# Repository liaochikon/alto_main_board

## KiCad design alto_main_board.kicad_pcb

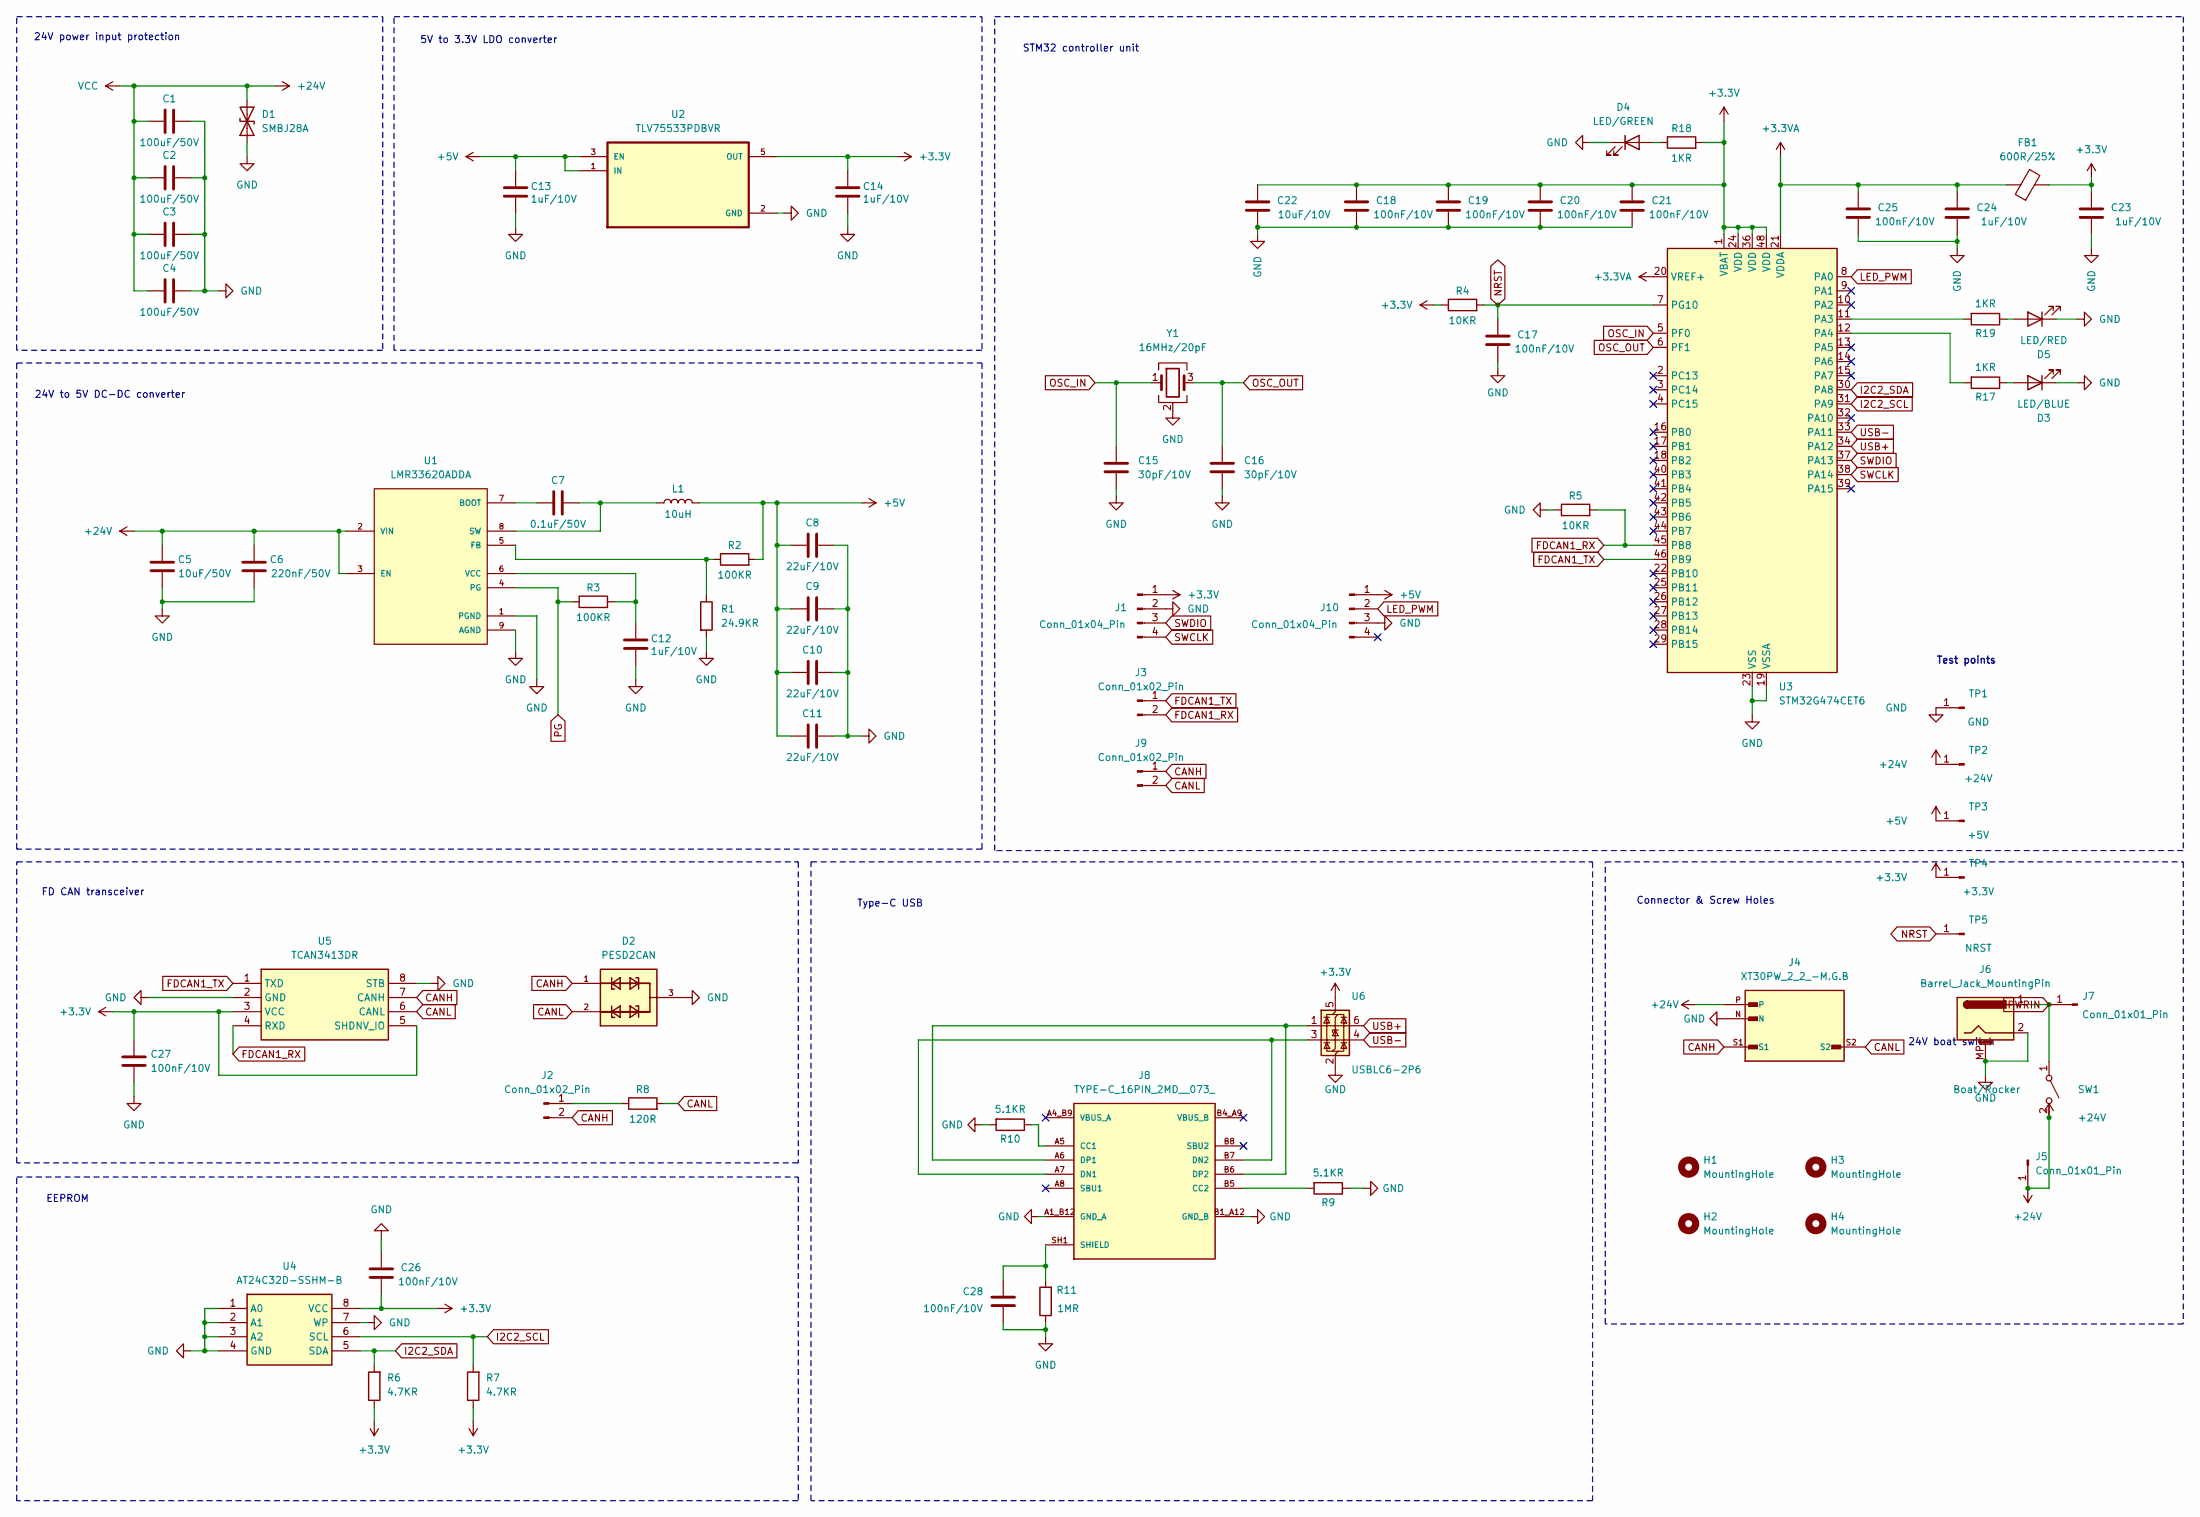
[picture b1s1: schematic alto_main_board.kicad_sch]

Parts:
C1, C2, C3, C4: 100uF/50V; C_1210_3225Metric
C5: 10uF/50V; C_0603_1608Metric
C6: 220nF/50V; C_0603_1608Metric
C7: 0.1uF/50V; C_0603_1608Metric
C8, C9, C10, C11: 22uF/10V; C_0603_1608Metric
C12, C13, C14, C23, C24: 1uF/10V; C_0603_1608Metric
C15, C16: 30pF/10V; C_0603_1608Metric
C17, C18, C19, C20, C21, C25, C26, C27, C28: 100nF/10V; C_0603_1608Metric
C22: 10uF/10V; C_0603_1608Metric
D1: SMBJ28A; D_SMB
D2: PESD2CAN; SOT95P230X110-3N
D3: LED/BLUE; LED_0603_1608Metric
D4: LED/GREEN; LED_0603_1608Metric
D5: LED/RED; LED_0603_1608Metric
FB1: 600R/25%; L_0603_1608Metric
H1, H2, H3, H4: MountingHole; MountingHole_3.2mm_M3
J1: Conn_01x04_Pin; PinHeader_1x04_P2.54mm_Vertical
J2, J3, J9: Conn_01x02_Pin; PinHeader_1x02_P2.54mm_Vertical
J4: XT30PW_2_2_-M.G.B; AMASS_XT30PW_2_2_-M.G.B; PARTREV NA
J5, J7: Conn_01x01_Pin; PinHeader_1x01_P2.54mm_Vertical
J6: Barrel_Jack_MountingPin; BarrelJack_Wuerth_694108106102_2.5x5.5mm
J8: TYPE-C_16PIN_2MD__073_; SHOUHAN_TYPE-C_16PIN_2MD__073_; PARTREV A
J10: Conn_01x04_Pin; JST_XH_B4B-XH-A_1x04_P2.50mm_Vertical
L1: 10uH; L_Chilisin_BWVS00505030
R1: 24.9KR; R_0603_1608Metric
R2, R3: 100KR; R_0603_1608Metric
R4, R5: 10KR; R_0603_1608Metric
R6, R7: 4.7KR; R_0603_1608Metric
R8: 120R; R_0603_1608Metric
R9, R10: 5.1KR; R_0603_1608Metric
R11: 1MR; R_0603_1608Metric
R17, R18, R19: 1KR; R_0603_1608Metric
SW1: Boat/Rocker
TP1: GND; PinHeader_1x01_P2.54mm_Vertical
TP2: +24V; PinHeader_1x01_P2.54mm_Vertical
TP3: +5V; PinHeader_1x01_P2.54mm_Vertical
TP4: +3.3V; PinHeader_1x01_P2.54mm_Vertical
TP5: NRST; PinHeader_1x01_P2.54mm_Vertical
U1: LMR33620ADDA; CONV_LMR33620ADDA; PARTREV C
U2: TLV75533PDBVR; SOT95P280X145-5N
U3: STM32G474CET6; LQFP-48_7x7mm_P0.5mm
U4: AT24C32D-SSHM-B; SOIC127P600X175-8N; Manufacturer_Part_Number AT24C32D-SSHM-B; Mouser Part Number 556-AT24C32D-SSHM-B
U5: TCAN3413DR; SOIC127P600X175-8N; Manufacturer_Part_Number TCAN3413DR; Mouser Part Number 595-TCAN3413DR
U6: USBLC6-2P6; SOT-23-6
Y1: 16MHz/20pF; Crystal_SMD_3225-4Pin_3.2x2.5mm

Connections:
+3.3V: C14.2, C18.1, C19.1, C20.1, C21.1, C22.1, C23.1, C26.2, C27.2, FB1.2, J1.1, R4.1, R6.1, R7.1, R18.2, TP4.1, U2.5 (OUT), U3.1 (VBAT), U3.24 (VDD), U3.36 (VDD), U3.48 (VDD), U4.8 (VCC), U5.3 (VCC), U5.5 (SHDNV_IO), U6.5 (VBUS)
+3.3VA: C24.1, C25.1, FB1.1, U3.20 (VREF+), U3.21 (VDDA)
+5V: C8.1, C9.1, C10.1, C11.1, C13.2, J10.1, L1.2, R2.2, TP3.1, U2.1 (IN), U2.3 (EN)
+24V: C1.1, C2.1, C3.1, C4.1, C5.1, C6.1, D1.2 (A2), J4.P, J5.1, SW1.2 (B), TP2.1, U1.2 (VIN), U1.3 (EN)
CANH: D2.1, J2.2, J4.S1, J9.1, U5.7 (CANH)
CANL: D2.2, J4.S2, J9.2, R8.2, U5.6 (CANL)
FDCAN1_RX: J3.2, R5.2, U3.45 (PB8), U5.4 (RXD)
FDCAN1_TX: J3.1, U3.46 (PB9), U5.1 (TXD)
GND: C1.2, C2.2, C3.2, C4.2, C5.2, C6.2, C8.2, C9.2, C10.2, C11.2, C12.1, C13.1, C14.1, C15.2, C16.2, C17.2, C18.2, C19.2, C20.2, C21.2, C22.2, C23.2, C24.2, C25.2, C26.1, C27.1, C28.2, D1.1 (A1), D2.3, D3.1 (K), D4.1 (K), D5.1 (K), J1.2, J4.N, J6.2, J6.MP (MountPin), J8.A1_B12 (GND_A), J8.B1_A12 (GND_B), J10.3, R1.2, R5.1, R9.1, R10.2, R11.1, TP1.1, U1.1 (PGND), U1.9 (AGND), U1.9_1 (AGND), U1.9_2 (AGND), U1.9_3 (AGND), U1.9_4 (AGND), U1.9_5 (AGND), U1.9_6 (AGND), U1.9_7 (AGND), U1.9_8 (AGND), U2.2 (GND), U3.19 (VSSA), U3.23 (VSS), U3.35 (VSS), U3.47 (VSS), U4.1 (A0), U4.2 (A1), U4.3 (A2), U4.4 (GND), U4.7 (WP), U5.2 (GND), U5.8 (STB), U6.2 (GND), Y1.2 (G), Y1.4 (G)
I2C2_SCL: R7.2, U3.31 (PA9), U4.6 (SCL)
I2C2_SDA: R6.2, U3.30 (PA8), U4.5 (SDA)
LED_PWM: J10.2, U3.8 (PA0)
unnamed: C28.1, J8.SH1 (SHIELD), J8.SH2 (SHIELD), J8.SH3 (SHIELD), J8.SH4 (SHIELD), R11.2
unnamed: D3.2 (A), R17.1
unnamed: D4.2 (A), R18.1
unnamed: D5.2 (A), R19.1
unnamed: J2.1, R8.1
unnamed: J6.1, J7.1, SW1.1 (A)
unnamed: J8.A5 (CC1), R10.1
unnamed: J8.B5 (CC2), R9.2
unnamed: J8.A7 (DN1), J8.B7 (DN2), U6.3 (I/O2)
unnamed: J8.A6 (DP1), J8.B6 (DP2), U6.1 (I/O1)
unnamed: C7.1, U1.7 (BOOT)
unnamed: R1.1, R2.1, U1.5 (FB)
unnamed: C7.2, L1.1, U1.8 (SW)
unnamed: C12.2, R3.2, U1.6 (VCC)
unnamed: R19.2, U3.11 (PA3)
unnamed: R17.2, U3.12 (PA4)
unnamed: C17.1, R4.2, TP5.1, U3.7 (PG10)
OSC_IN: C15.1, U3.5 (PF0), Y1.1
OSC_OUT: C16.1, U3.6 (PF1), Y1.3
PG: R3.1, U1.4 (PG)
SWCLK: J1.4, U3.38 (PA14)
SWDIO: J1.3, U3.37 (PA13)
USB+: U3.34 (PA12), U6.6 (I/O1)
USB-: U3.33 (PA11), U6.4 (I/O2)

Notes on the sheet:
Type-C USB
Connector & Screw Holes
24V to 5V DC-DC converter
5V to 3.3V LDO converter
EEPROM
24V power input protection
FD CAN transceiver
STM32 controller unit
24V boat switch
Test points

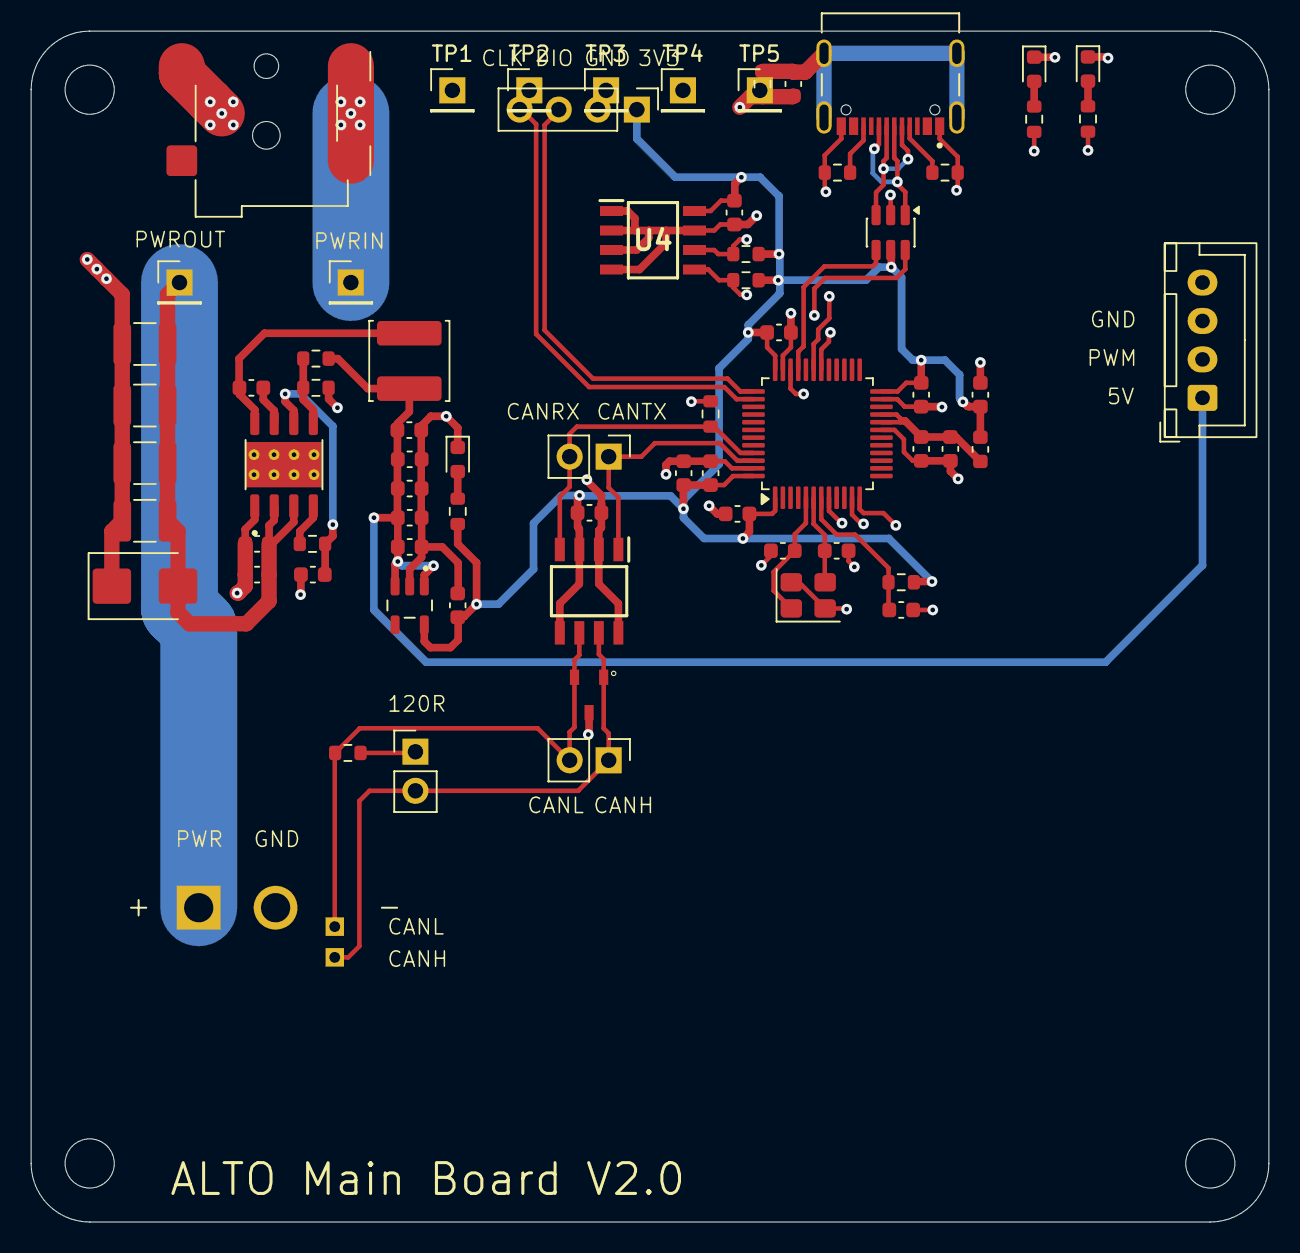
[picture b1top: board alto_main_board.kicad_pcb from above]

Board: 4 copper layers, 80.5 x 77.5 mm, 75 parts (0 on the bottom side), 36 nets.

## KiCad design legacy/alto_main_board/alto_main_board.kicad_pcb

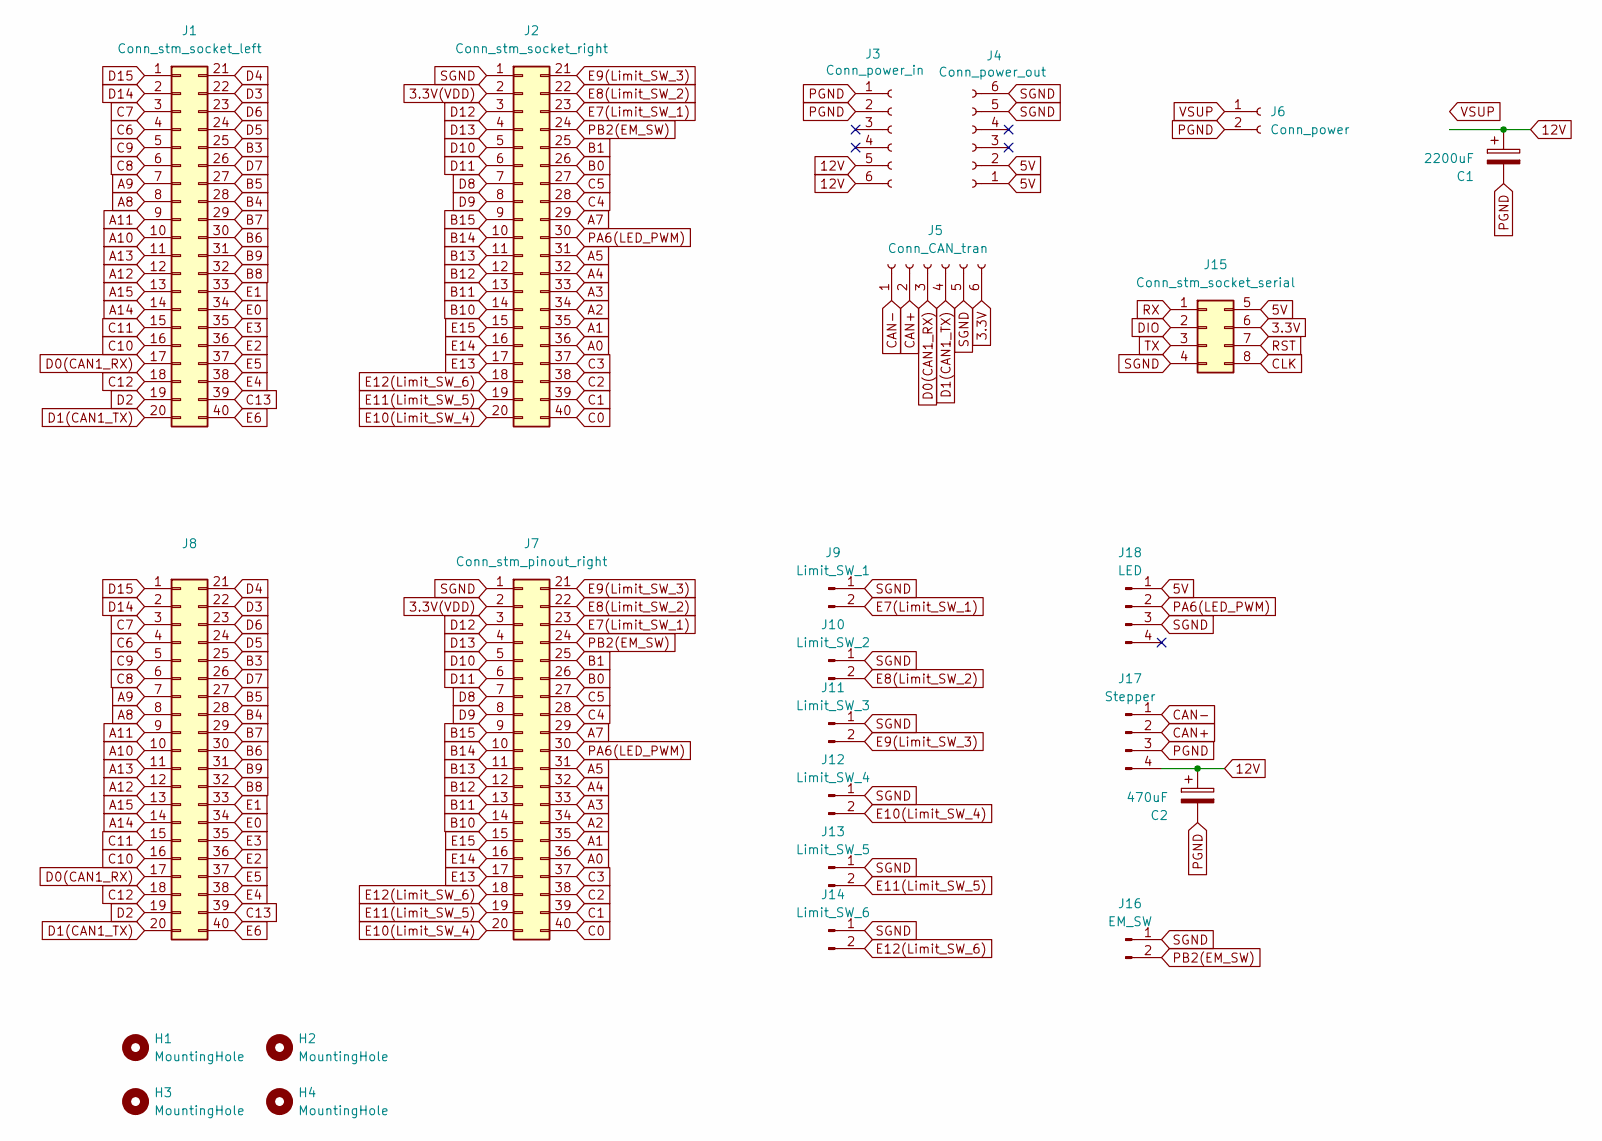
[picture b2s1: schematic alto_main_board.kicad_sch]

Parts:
C1: 2200uF; CP_Radial_D13.0mm_P5.00mm
C2: 470uF; CP_Radial_D8.0mm_P3.50mm
H1, H2, H3, H4: MountingHole; MountingHole_3.2mm_M3_Pad
J1: Conn_stm_socket_left; PinSocket_2x20_P2.54mm_Vertical
J2: Conn_stm_socket_right; PinSocket_2x20_P2.54mm_Vertical
J3: Conn_power_in; PinSocket_1x06_P2.54mm_Vertical
J4: Conn_power_out; PinSocket_1x06_P2.54mm_Vertical
J5: Conn_CAN_tran; PinSocket_1x06_P2.54mm_Vertical
J6: Conn_power; BarrelJack_Wuerth_694108106102_2.5x5.5mm
J7: Conn_stm_pinout_right; PinSocket_2x20_P2.54mm_Vertical
J8: Conn_stm_pinout_left; PinSocket_2x20_P2.54mm_Vertical
J9: Limit_SW_1; PinHeader_1x02_P2.54mm_Vertical
J10: Limit_SW_2; PinHeader_1x02_P2.54mm_Vertical
J11: Limit_SW_3; PinHeader_1x02_P2.54mm_Vertical
J12: Limit_SW_4; PinHeader_1x02_P2.54mm_Vertical
J13: Limit_SW_5; PinHeader_1x02_P2.54mm_Vertical
J14: Limit_SW_6; PinHeader_1x02_P2.54mm_Vertical
J15: Conn_stm_socket_serial; PinSocket_2x04_P2.54mm_Vertical
J16: EM_SW; PinHeader_1x02_P2.54mm_Vertical
J17: Stepper; PinHeader_1x04_P2.54mm_Vertical
J18: LED; PinHeader_1x04_P2.54mm_Vertical

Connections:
3.3V: J5.6, J15.6
3.3V(VDD): J2.2, J7.2
5V: J4.1, J4.2, J15.5, J18.1
12V: C1.1, C2.1, J3.5, J3.6, J17.4; also elsewhere on the board
A0: J2.36, J7.36
A1: J2.35, J7.35
A2: J2.34, J7.34
A3: J2.33, J7.33
A4: J2.32, J7.32
A5: J2.31, J7.31
A7: J2.29, J7.29
A8: J1.8, J8.8
A9: J1.7, J8.7
A10: J1.10, J8.10
A11: J1.9, J8.9
A12: J1.12, J8.12
A13: J1.11, J8.11
A14: J1.14, J8.14
A15: J1.13, J8.13
B0: J2.26, J7.26
B1: J2.25, J7.25
B3: J1.25, J8.25
B4: J1.28, J8.28
B5: J1.27, J8.27
B6: J1.30, J8.30
B7: J1.29, J8.29
B8: J1.32, J8.32
B9: J1.31, J8.31
B10: J2.14, J7.14
B11: J2.13, J7.13
B12: J2.12, J7.12
B13: J2.11, J7.11
B14: J2.10, J7.10
B15: J2.9, J7.9
C0: J2.40, J7.40
C1: J2.39, J7.39
C2: J2.38, J7.38
C3: J2.37, J7.37
C4: J2.28, J7.28
C5: J2.27, J7.27
C6: J1.4, J8.4
C7: J1.3, J8.3
C8: J1.6, J8.6
C9: J1.5, J8.5
C10: J1.16, J8.16
C11: J1.15, J8.15
C12: J1.18, J8.18
C13: J1.39, J8.39
CAN+: J5.2, J17.2
CAN-: J5.1, J17.1
CLK: J15.8
D0(CAN1_RX): J1.17, J5.3, J8.17
D1(CAN1_TX): J1.20, J5.4, J8.20
D2: J1.19, J8.19
D3: J1.22, J8.22
D4: J1.21, J8.21
D5: J1.24, J8.24
D6: J1.23, J8.23
D7: J1.26, J8.26
D8: J2.7, J7.7
D9: J2.8, J7.8
D10: J2.5, J7.5
D11: J2.6, J7.6
D12: J2.3, J7.3
D13: J2.4, J7.4
D14: J1.2, J8.2
D15: J1.1, J8.1
DIO: J15.2
E0: J1.34, J8.34
E1: J1.33, J8.33
E2: J1.36, J8.36
E3: J1.35, J8.35
E4: J1.38, J8.38
E5: J1.37, J8.37
E6: J1.40, J8.40
E7(Limit_SW_1): J2.23, J7.23, J9.2
E8(Limit_SW_2): J2.22, J7.22, J10.2
E9(Limit_SW_3): J2.21, J7.21, J11.2
E10(Limit_SW_4): J2.20, J7.20, J12.2
E11(Limit_SW_5): J2.19, J7.19, J13.2
E12(Limit_SW_6): J2.18, J7.18, J14.2
E13: J2.17, J7.17
E14: J2.16, J7.16
E15: J2.15, J7.15
PA6(LED_PWM): J2.30, J7.30, J18.2
PB2(EM_SW): J2.24, J7.24, J16.2
PGND: C1.2, C2.2, J3.1, J3.2, J6.2, J17.3
RST: J15.7
RX: J15.1
SGND: J2.1, J4.5, J4.6, J5.5, J7.1, J9.1, J10.1, J11.1, J12.1, J13.1, J14.1, J15.4, J16.1, J18.3
TX: J15.3
VSUP: J6.1; also elsewhere on the board

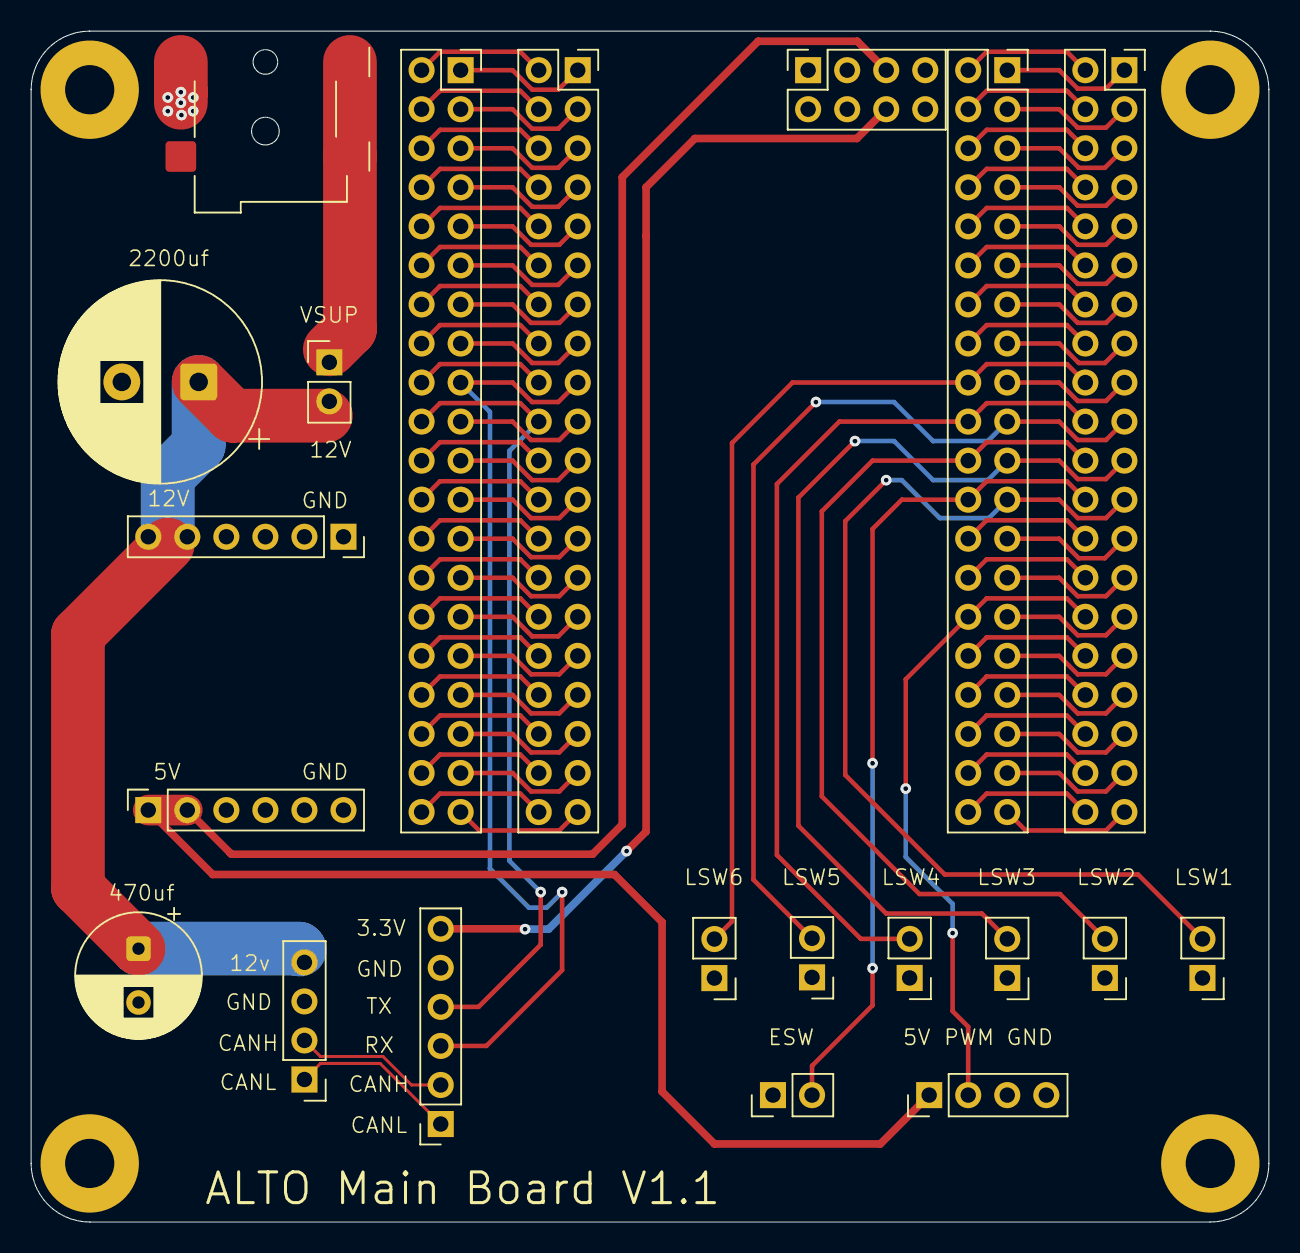
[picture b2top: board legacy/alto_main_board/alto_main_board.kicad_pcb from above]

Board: 2 copper layers, 80.5 x 77.5 mm, 25 parts (0 on the bottom side), 87 nets.

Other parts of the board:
J19: Conn_pwr; PinHeader_1x02_P2.54mm_Vertical

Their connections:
12V: J19.2; also elsewhere on the board
VSUP: J19.1; also elsewhere on the board

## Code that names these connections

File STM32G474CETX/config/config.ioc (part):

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Mcu.Name=STM32G474C(B-C-E)Tx
Mcu.Package=LQFP48
Mcu.UserName=STM32G474CETx
PA0.GPIOParameters=GPIO_Label
PA0.GPIO_Label=LED_PWM
PA0.Signal=S_TIM2_CH1
PA11.Mode=Device
PA11.Signal=USB_DM
PA12.Mode=Device
PA12.Signal=USB_DP
PA13.Mode=Serial_Wire
PA13.Signal=SYS_JTMS-SWDIO
PA14.Mode=Serial_Wire
PA14.Signal=SYS_JTCK-SWCLK
PA3.GPIOParameters=GPIO_Label
PA3.GPIO_Label=RED_LED
PA3.Signal=GPIO_Output
PA4.GPIOParameters=GPIO_Label
PA4.GPIO_Label=BLUE_LED
PA4.Signal=GPIO_Output
PA8.Mode=I2C
PA8.Signal=I2C2_SDA
PA9.Mode=I2C
PA9.Signal=I2C2_SCL
PB8-BOOT0.Mode=FDCAN_Activate
PB8-BOOT0.Signal=FDCAN1_RX
PB9.Mode=FDCAN_Activate
PB9.Signal=FDCAN1_TX
PF0-OSC_IN.Mode=HSE-External-Oscillator
PF0-OSC_IN.Signal=RCC_OSC_IN
PF1-OSC_OUT.Mode=HSE-External-Oscillator
PF1-OSC_OUT.Signal=RCC_OSC_OUT
RCC.HSE_VALUE=16000000
RCC.SYSCLKFreq_VALUE=160000000
RCC.SYSCLKSource=RCC_SYSCLKSOURCE_PLLCLK
board=custom

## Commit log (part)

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2026-03-25 0325
2026-04-04 0404
2026-04-05 0405
2026-04-24 0424
